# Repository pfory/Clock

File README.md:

# Clock

4 digit LED display with TM1637 and ESP8266 for time sync via internet

- 0.36/0.56" inch TM1637 LED Clock Tube Display for Arduino Red/Blue/Green/White
- wemos D1 mini

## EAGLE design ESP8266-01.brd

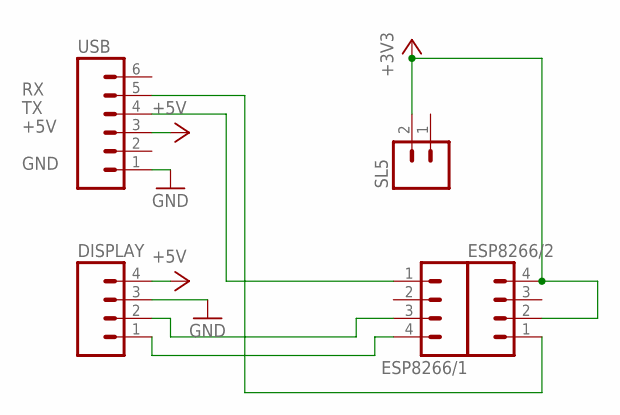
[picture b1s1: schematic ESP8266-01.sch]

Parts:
DISPLAY: M04; 04P
ESP8266/1, ESP8266/2: M04; 04P
SL5: M02; 02P
USB: M06; 06P

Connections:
+3V3: ESP8266/2.2, ESP8266/2.4, SL5.2
+5V: DISPLAY.4, USB.3
GND: DISPLAY.3, USB.1
unnamed: DISPLAY.2, ESP8266/1.3
unnamed: DISPLAY.1, ESP8266/1.4
RX: ESP8266/2.1, USB.5
TX: ESP8266/1.1, USB.4

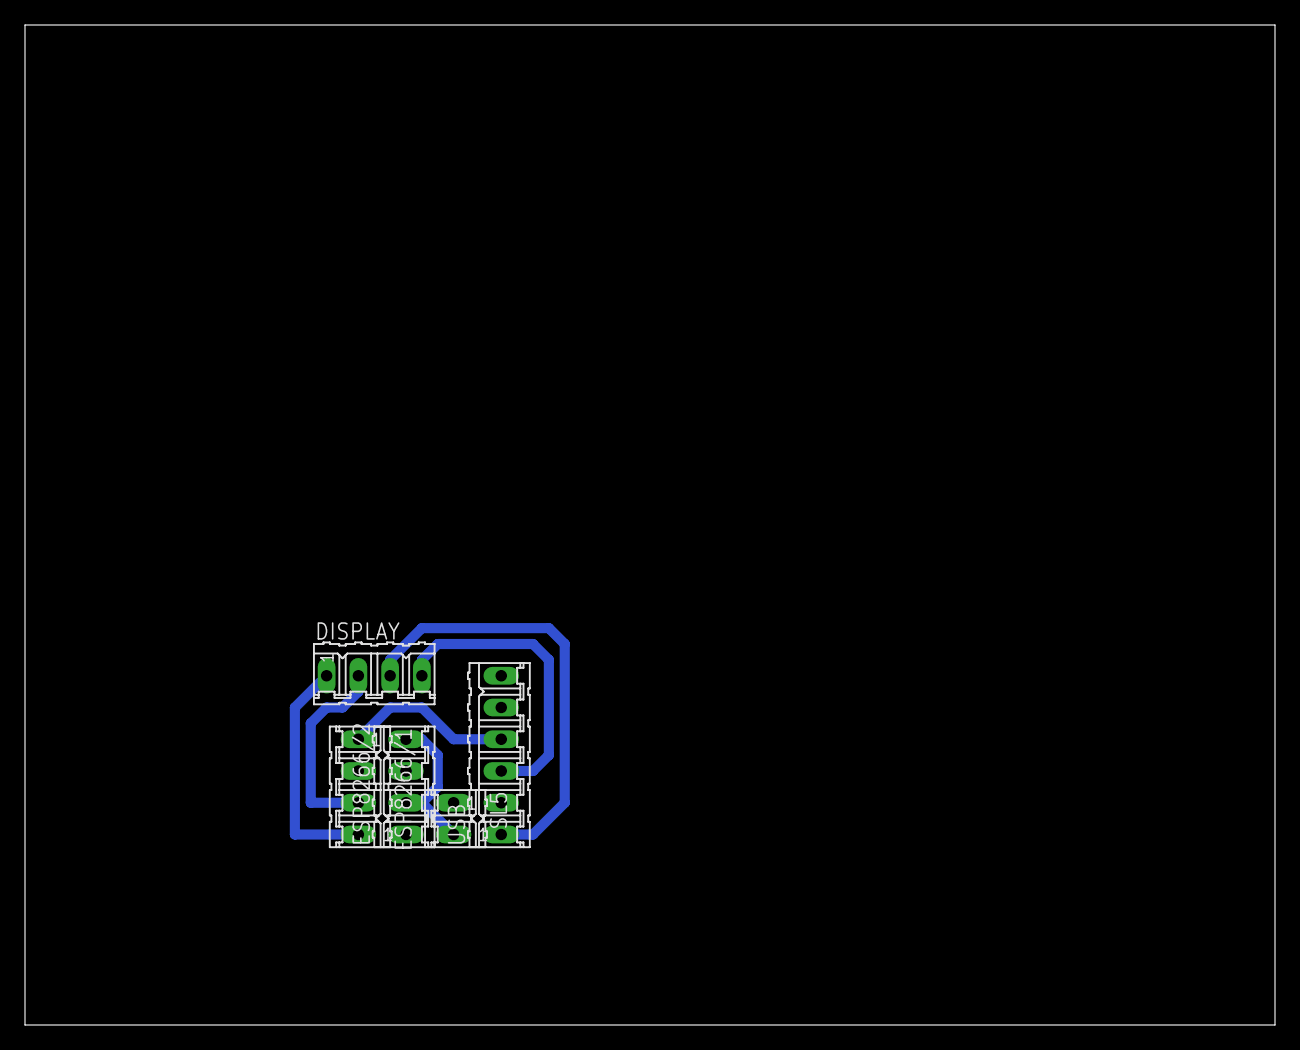
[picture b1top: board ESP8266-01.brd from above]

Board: 2 copper layers, 100.0 x 80.0 mm, 5 parts (0 on the bottom side), 7 nets.

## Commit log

2018-12-06 init
2018-12-07 optimalizace
2019-05-16 teplota
2019-05-17 upravy pro jinou knihovnu
2019-06-18 verze pro ESP8266-01
2019-11-11 uprava zobrazovani teplot nastaveni pres mqtt povel - reset a brightness
2019-11-18 nahrano do clock2 - loznice
2019-11-27 + sw na velké hodiny
2019-11-27 add credencials
2019-11-29 upravy
2020-03-22 funkcni verze velkych hodin
2020-04-30 +ota
2020-11-27 wifimanager
2021-01-29 + Configuration.h
2021-01-29 v 2.00
2021-02-10 opravena chyba při zobrazování teplot < -10
2021-02-18 opravena chyba se zobrazenim teploty 10 stupnu
2021-03-22 stridani pocasi a casu na zaklade vnitrniho timeru
2021-03-23 1.04
2021-03-24 1.05
2021-04-20 v2.10 + měření teploty místnosti
2021-05-17 osekana testovaci verze
2021-05-19 + reconnect 2 wifi
2021-05-19 1.11
2021-05-19 brightness
2021-05-26 odesilani IP a MAC na zacatku a na vyzadani
2021-08-10 verze
2021-08-17 kdyz se prijimaji dta atak se neodesilaji data
2021-11-25 uprava kvuli odpojovani wifi
2021-11-26 + pridano zobrazeni vlhkosti a tlaku
2021-11-30 vylepsene wifi
2021-11-30 + config portal
2021-11-30 + ap name
2021-12-07 2.31
2021-12-10 2.32
2021-12-11 oprava posilani teplot
2021-12-11 oprava registrace zmeny jasu
2023-12-11 řízení jasu
2023-12-13 upravy jasu
2023-12-14 vynechani prvni nuly
2023-12-18 odtsraněno minus v hodinách
2023-12-20 nezobrazeni nuly pro hodiny < 10 pro CLOCK1
2024-01-30 time server local
2024-08-06 pridani vnitrni teploty a vlhkosti pro hodiny koupelna
